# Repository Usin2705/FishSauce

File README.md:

# Wall-F
<b>IoT project 2018</b>  
Metropolia UAS, 2018.  
Team members: Nhan Tran, JingXuan Wu, Nhan Phan.  

<b>Intro video</b>  

Hardware:  
Raspberry Pi3 B+ (with RPi camera module, microphone, mini speaker). Powered by power bank.  
LPC1549 LPCXpresso board (with 2 Ultrasonic Sensors, 2 Servo Motors, 2 L298N Motor Drivers, 1 HC-12 Wireless Serial Port Communication Module, 1 LED). Powered by power bank.  

4 Omni Wheels with 4 9V DC motors (with Hall Sensor), steel frames, wood frames with laser engraved (from another Metropolia school project), switches, 3D printed mount, steel hinge. Powered by 8 1.2V, 2800mAh Ni-MH batteries.  

Funduino Joystick Shield (not showed in the video) with HC-12 Wireless Serial Port Communication Module. Powered by 9V battery.  

3 ESP32 LOLIN D32 Pro V2.0.0 (not showed in the video). Intended to be used as BLE beacons for indoor positioning, but not managed to including it in the end of the course (worked but need a lot of improvements).  

<b>Voice recognition</b>  

RPi captures the voice command via microphone, save it as a "wav" file. The file then uploaded to Google Cloud, using Google Cloud Speech-to-Text to translate the voice to text strings. RPi receives the text strings from Google Cloud and processing the text string to identify the correct command. RPi reply using mini speakek, and send command to LPC1549 via Uart.  

Because the time to upload the "wav" file and then received the text string back is long (due to internet speed and Google's processing speed), we used 1 LED to indicate the robot is "thinking".  

Note: due to Google Cloud Speech-to-Text is a paid service (only free for 1,000 requests/month), a mini switch is used to toogle on/off this Voice recognition module. 

In the video you can see that Wall-F recognizes the voice command from our team member and reply back.  

<b>Voice command</b>  

In this video Wall-F move according to the command from user.  

We add some improvement for the speech recognition module. We hard code synonyms ("turn", "rotate") so the car can understand our intention easier. Because our English is not as good as native speak,We also added some adjustment to the module as well (Our "turn", "done" is very similar).  

In the video, you can see our team member holding a wooden board. That is to demostrate our ultrasonic sensors. We have 1 in the front, right beside the camera, and 1 in the back. If the ultrasonic sensors detect obstacle in front or back, it will block the car movement in that direction. However, you still see it can hit the wall if the angle is too low (as the waves take longer time to travel back). This is the common limitation of ultrasonic sensors. You can either add more ultrasonics sensors to the cars, or idealy buy or make a 360° ultrasonic sensors, if you want to solve this problem.  

We can also use LiDAR sensor to improve it 360° long range detection. Howver, LiDAR can't detect objects in short range so we still need to rely on Ultrasonic sensors.  

<b>Face Recognition</b>  

We trained our Wall-F using our team member's face and our instructor's face, so it can recognize 4 different face together. If it see a familiar face Wall-F will speak out loud his/her name.  

The Face Recognition have two steps. The first step is "Face Detection" using Haar Feature-based Cascade Classifiers. After detect all face available in the picture, in step 2, it will pass all faces image to our trained data. If the face image is similar to what we have trained it, it will "recognize" the face and output the result. Otherwise the face will be labeled as "Unknown". The key point here is to edit the "tolerance" level, high tolerance will make the model wrongly recognize unknown face as our faces, while low tolerance make it more difficult to recognized a trained face.  

In this video, aside from Face Recognition, you can also see Wall-F face tracking module. We programmed it so that it will track the face of one of our members (Nhan Phan), and will also move the camera so that his face is placed in the center of the picture. If it is tracking his face and Nhan moved out of the camera, it will move the camera around to look for him.  

<b>Face Following</b>  

Wall-F also have a different mode called "Face Following". If this mode is turn on (using voice control), it will stop all face Tracking, and move the camera upward. Upon regconized the face of our team member, it will move closer to him. Howver, in reality, the RPi camera is not good with handling ligth from lightbulbs in the celling (and we have a lot of celling lights in our school). As a result, picture took by the RPi when the camera moving up is very difficult to see, and make face recognition from those picture almost impossible.  

<b>Streaming to TV</b>  

This video is just to demostate the ability to steam the video to any IoT devices. In this case it's our smart TV. As long as they share the same network, we can log in the video feed to see real time data from Wall-F.  

Link to the LPC1549 codes, which handle the commands sent from Raspberry Pi 3, commands from HC-12 wireless module, control the motors, camera and ultrasonic sensor: https://github.com/Usin2705/FishSauce/tree/master/LPCmotor  

Link to the Raspberry Pi3 codes, which contain several sub packages (UartCommunication: Uart communication with LPC1549, camModule: handle the face regconition, speechRegModule: handle the connection with Google Cloud Service and handle the voice control from users, ttsModule: allow Wall-F to speak using a mini speaker, and textVerifyModule: utility modules help with the voice regconition): https://github.com/Usin2705/FishSauce/tree/master/RaspberryPi3. All sub packages are then grouped together and run with multiprocessing library in Python. Heavy modules (voice regconition and face regconition) are run using bash script startVoiceCam.sh, other modules is run via startMotor.sh.  

Repository also contains other features. Some which we wanted to implement but were not finished due to time constraint. BLE indoor positioning is one of those. While we managed to make it work, its accuracy did not satisfy our requirement. And we did not have time to make adjustment (or experimenting with others BLE device) to improve it.
   
<b>Schematic</b>  

Actual PCB, this was done much later after our project, as our PCB machine was broken at the time. And we do not have enough budget and time for the PCB. The PCBs here are made by https://jlcpcb.com/, and they arrived near the summer of 2019.

Excellent work from my teammate in designing the PCB. It has no big error when we connect all the cables, LEDs and Buttons. Our Wall-F look a lot nicer than before.

# License

Copyright 2018

Licensed under the Apache License, Version 2.0 (the "License");
you may not use this file except in compliance with the License.
You may obtain a copy of the License at

   http://www.apache.org/licenses/LICENSE-2.0

Unless required by applicable law or agreed to in writing, software
distributed under the License is distributed on an "AS IS" BASIS,
WITHOUT WARRANTIES OR CONDITIONS OF ANY KIND, either express or implied.
See the License for the specific language governing permissions and
limitations under the License.

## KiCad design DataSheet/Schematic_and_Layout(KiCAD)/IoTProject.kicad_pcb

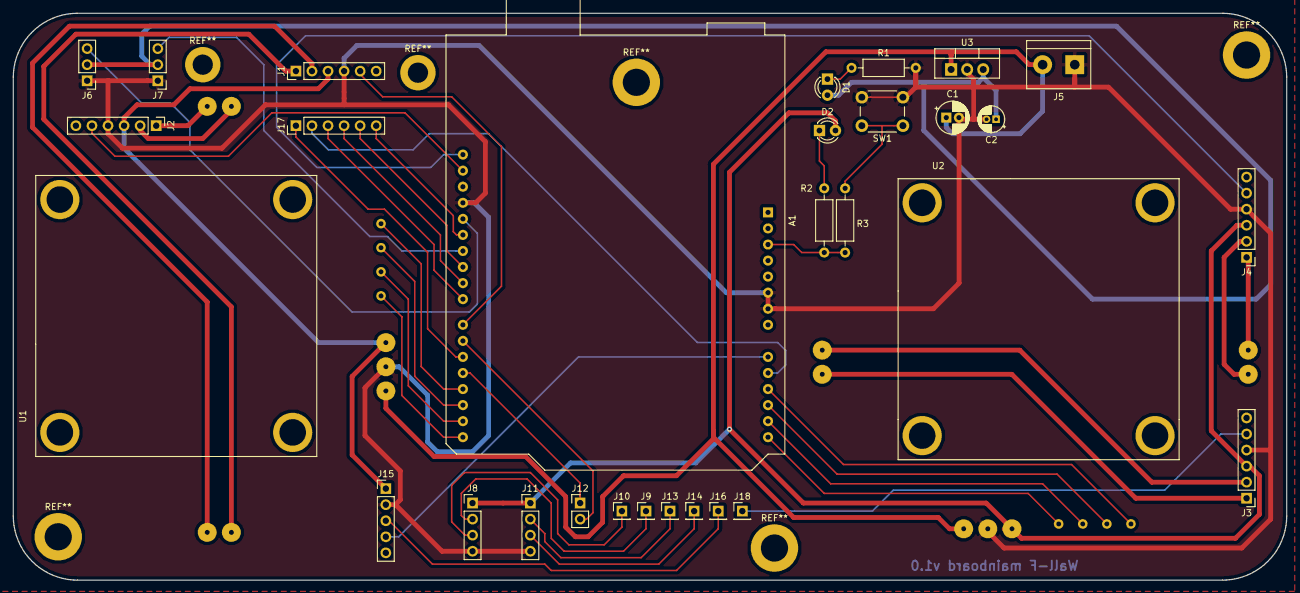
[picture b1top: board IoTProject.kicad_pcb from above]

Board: 2 copper layers, 201.4 x 89.7 mm, 30 parts (0 on the bottom side), 45 nets.

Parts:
A1: LPCXpresso1549; Arduino_UNO_R3
C1: 0.33uF; CP_Radial_D5.0mm_P2.00mm
C2: 104 ceramic; CP_Radial_D4.0mm_P1.50mm
D1: 5VU3 LED; LED_D3.0mm
D2: reset LED; LED_D3.0mm
J1: north motor; PinHeader_1x06_P2.54mm_Vertical
J2: south motor; PinHeader_1x06_P2.54mm_Vertical
J3: east motor; PinHeader_1x06_P2.54mm_Vertical
J4: west motor; PinHeader_1x06_P2.54mm_Vertical
J5: 9 -12V Input; TerminalBlock_bornier-2_P5.08mm
J6: servo_updown; PinHeader_1x03_P2.54mm_Vertical
J7: servo_leftright; PinHeader_1x03_P2.54mm_Vertical
J8: ultrasonic front; PinHeader_1x04_P2.54mm_Vertical
J9: P1_4 trig fron; PinHeader_1x01_P2.54mm_Vertical
J10: P1_6 ech fron; PinHeader_1x01_P2.54mm_Vertical
J11: ultrasonic rear; PinHeader_1x04_P2.54mm_Vertical
J12: Pi's UART; PinHeader_1x02_P2.54mm_Vertical
J13: P1_5 trig rear; PinHeader_1x01_P2.54mm_Vertical
J14: P1_7 ech rear; PinHeader_1x01_P2.54mm_Vertical
J15: HC12 module; PinHeader_1x05_P2.54mm_Vertical
J16: P1_1 LPCs TX; PinHeader_1x01_P2.54mm_Vertical
J17: extender; PinHeader_1x06_P2.54mm_Vertical
J18: extenfer P1_0; PinHeader_1x01_P2.54mm_Vertical
R1: 1k; R_Axial_DIN0207_L6.3mm_D2.5mm_P10.16mm_Horizontal
R2: 2.2k; R_Axial_DIN0207_L6.3mm_D2.5mm_P10.16mm_Horizontal
R3: 100R; R_Axial_DIN0207_L6.3mm_D2.5mm_P10.16mm_Horizontal
SW1: SW_Push; SW_PUSH_6mm
U1, U2: L298module; l298module
U3: L7805; TO-220-3_Vertical

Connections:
5VU1: J1.3, J2.3, J15.1, U1.3
5VU2: D2.2, J3.3, J4.3, J8.1, J11.1, U2.3
5VU3: C2.1, D1.2, J6.2, J7.2, U3.3
12V: C1.1, J5.2, U1.1, U2.1, U3.1
A1: A1.10, J17.2
Earth: A1.6, A1.7, A1.29, C1.2, C2.2, J1.4, J2.4, J3.4, J4.4, J5.1, J6.1, J7.1, J8.4, J11.4, J15.2, R1.2, SW1.2, U1.2, U2.2, U3.2
unnamed: A1.3, R2.2, R3.2
unnamed: A1.20, J17.1
unnamed: A1.23, J17.3
unnamed: A1.24, J17.4
unnamed: A1.25, J17.5
unnamed: A1.27, J17.6
unnamed: D1.1, R1.1
unnamed: D2.1, R2.1
unnamed: R3.1, SW1.1
RX: J15.3, J16.1
RX_Pi: A1.19, J12.1
TX: A1.9, J15.4
TX_Pi: A1.21, J12.2
eastP0_6: A1.13, U2.5
eastP0_7: A1.14, U2.4
eastP1_0: J3.5, J18.1
east_out1: J3.2, U2.8
east_out2: J3.1, U2.9
echo_front: J8.3, J10.1
echo_rear: J11.3, J14.1
northP0_0: A1.22, J1.5
northP1_9: A1.16, U1.5
northP1_10: A1.15, U1.4
north_out1: J1.2, U1.8
north_out2: J1.1, U1.9
servo_leftright: A1.26, J7.3
servo_updown: A1.28, J6.3
southP0_9: A1.18, U1.7
southP0_23: A1.31, J2.5
southP0_29: A1.17, U1.6
south_out1: J2.2, U1.10
south_out2: J2.1, U1.11
trig_front: J8.2, J9.1
trig_rear: J11.2, J13.1
westP0_5: A1.12, U2.6
westP0_22: A1.32, J4.5
westP1_8: A1.11, U2.7
west_out1: J4.2, U2.10
west_out2: J4.1, U2.11

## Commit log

2018-10-24 feat: initial commit
2018-10-24 LPC motor move
2018-10-24 feat: added code from raspberry pi for face recognition
2018-10-24 feat: motor work properly
2018-10-24 feat: update capture.py function
2018-10-25 feat: added proper class for OmniWheel and OmniCar
2018-10-25 fix: turn bug
2018-10-26 feat: add Raspberrpi commnunication (not working)
2018-10-27 modify omniwheel.cpp: add interrupt pin to wheel, setup interrupt has not been tested yet because cannot add lpc15xx/inc include path which contains pinint.h
2018-10-29 finish the interrupt stuff but this yields some conflicts with the driving principal
2018-10-31 feat: added HC-12 communicaiton.
2018-11-05 add interrupt stopping mechanism for the wheels and change pins for south and west wheel
2018-11-06 feat: add tts and move (in one code)
2018-11-07 added and tested pulse mechanism for motors
2018-11-07 added and tested pulse mechanism for the wheels, the car now can move wheels independently
2018-11-08 feat: added servo control (not finish)
2018-11-08 feat: add measurement for pi camera, might need to change the X (750 and 2450 is already the maximum)
2018-11-09 feat: added camera control + movement control (arrow keys still have some error)
2018-11-14 feat: advertisement & scan for the RSSI and distance
2018-11-14 feat: add the complied library
2018-11-19 feat: add updated speechRegModule
2018-11-19 clean github
2018-11-20 feat: add more voice command
2018-11-27 feat: add Cam+voice
2018-12-04 fead: add some minor info
2018-12-05 feat: added 2nd uart
2018-12-05 bug: fixed joystick bug
2018-12-05 update code anh Nhan
2018-12-05 feat: added minor changes and Ultrasonic 1.0
2018-12-05 feat: almost done (need to improve the sensor)
2018-12-08 feat: add better ultrasonic sensor
2018-12-08 feat: added smoothing for ultrasonic sensor
2018-12-24 add schematic
2018-12-25 feat: added schematic pdf file
2018-12-27 add KiCAD schematic and layout files
2019-01-06 add sample images
2019-01-06 add the schematic image back
2019-02-11 add gerber files
2019-12-04 feat: add PCB images discard BLE changes (why it not as good as we think it should?)
2019-12-18 DOC: add better thumbnail
